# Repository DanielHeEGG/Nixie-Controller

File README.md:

# Nixie-Controller
Yet another nixie clock controller.

See [Hackaday Page](https://hackaday.io/project/180811-open-nixie-controller) for more details.

This project is archived, development is continuing in [v2](https://github.com/DanielHeEGG/Nixie-Controller-v2).

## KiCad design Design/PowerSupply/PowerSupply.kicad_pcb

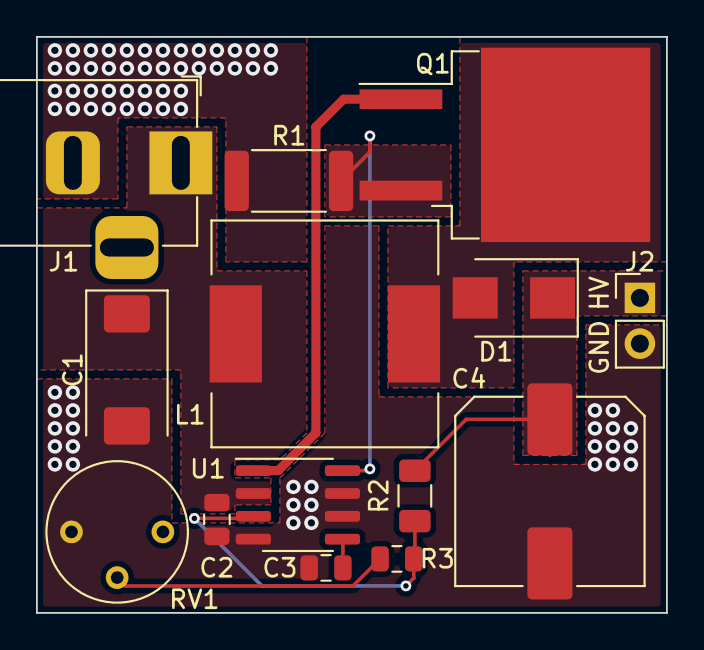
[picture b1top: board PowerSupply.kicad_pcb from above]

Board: 2 copper layers, 35.0 x 32.0 mm, 15 parts (1 on the bottom side), 9 nets.

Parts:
C1: 100uF,Low ESR; CP_EIA-7343-31_Kemet-D
C2, C3: 100nF; C_0805_2012Metric
C4: 10uF,250V; CP_Elec_10x10
CAUTION: Symbol_HighVoltage_Type2_CopperTop_VerySmall
D1: 300V, 2A, Fast Trr; D_SMB
J1: Barrel_Jack; BarrelJack_Horizontal
J2: Conn_01x02_Male; PinHeader_1x02_P2.54mm_Vertical
L1: 100uH,2A; L_12x12mm_H4.5mm
Q1: IRF644; TO-263-2
R1: 0.05,1W; R_2512_6332Metric
R2: 1M2,250V; R_1206_3216Metric
R3: 10K; R_0805_2012Metric
RV1: 10K; Potentiometer_Bourns_3339P_Vertical
U1: MAX1771; SOIC-8_3.9x4.9mm_P1.27mm

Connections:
+12V: C1.1, C2.1, J1.1, L1.1, U1.2
+180V: C4.1, D1.1, J2.1, R2.1
GND: C1.2, C2.2, C3.2, C4.2, J1.2, J2.2, R1.2, RV1.3, U1.4, U1.6, U1.7
unnamed: C3.1, U1.5
unnamed: D1.2, L1.2, Q1.2
unnamed: Q1.1, U1.1
unnamed: Q1.3, R1.1, U1.8
unnamed: R2.2, R3.1, U1.3
unnamed: R3.2, RV1.2

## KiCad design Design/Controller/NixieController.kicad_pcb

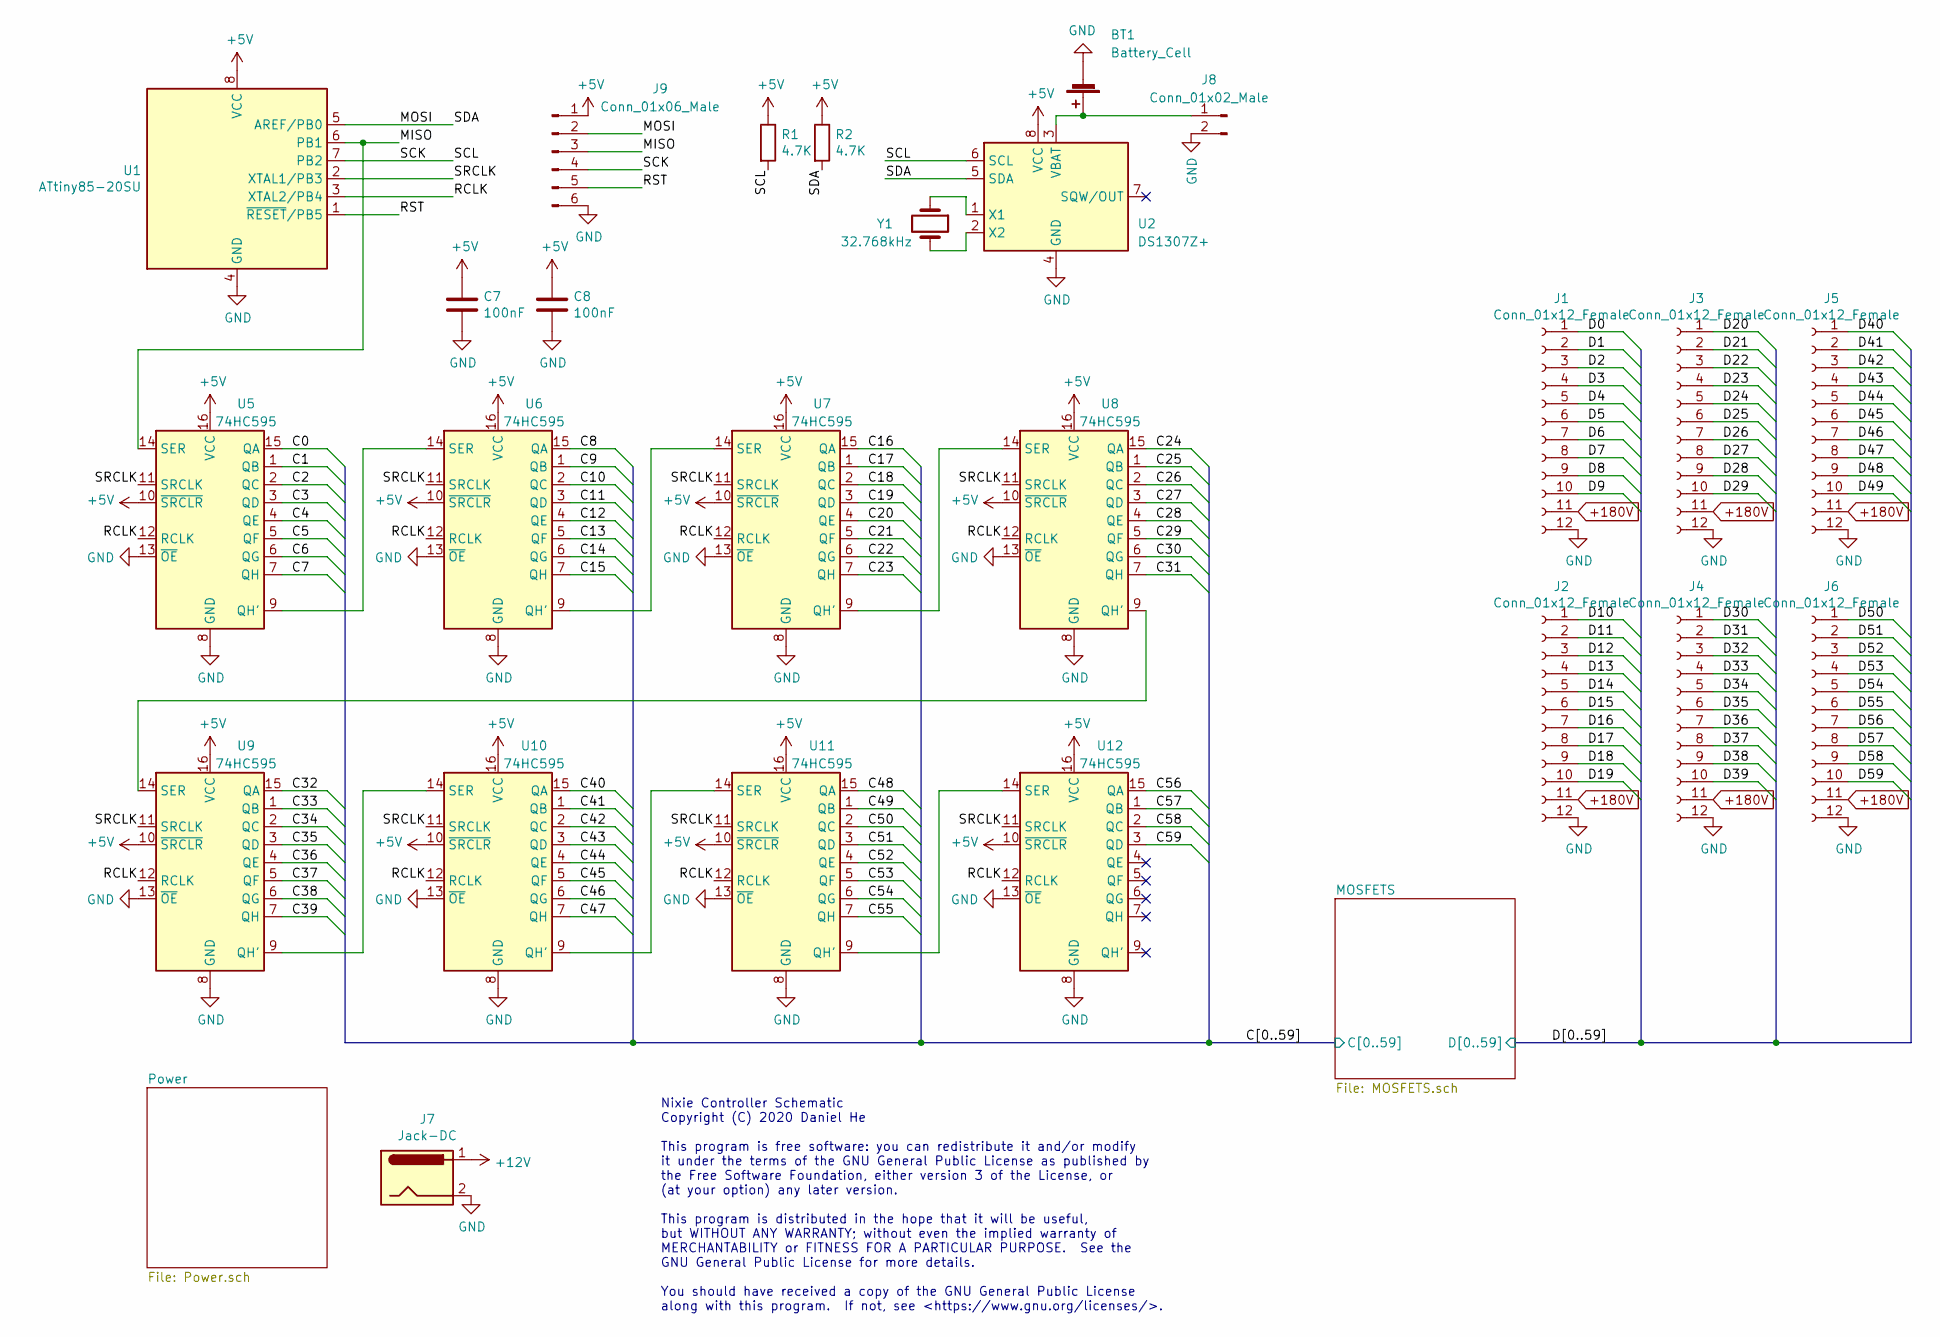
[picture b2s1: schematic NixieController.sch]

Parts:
BT1: Battery_Cell; Keystone_1056
C7, C8: 100nF; C_0805_2012Metric; Digikey # 1276-1007-6-ND
J1, J2, J3, J4, J5, J6: Conn_01x12_Female; PinSocket_1x12_P2.54mm_Vertical
J7: Jack-DC; BarrelJack_Horizontal; Digikey # 2092-KLDX-0202-A-ND
J8: Conn_01x02_Male; PinHeader_1x02_P2.54mm_Vertical
J9: Conn_01x06_Male; PinHeader_1x06_P2.54mm_Vertical
R1, R2: 4.7K; R_0805_2012Metric; Digikey # 311-4.7KARDKR-ND
U1: ATtiny85-20SU; SOIC-8_5.275x5.275mm_P1.27mm; Digikey # ATTINY85-20SURDKR-ND
U2: DS1307Z+; SOIC-8_3.9x4.9mm_P1.27mm; Digikey # DS1307Z+T&RDKR-ND
U5, U6, U7, U8, U9, U10, U11, U12: 74HC595; SOIC-16_3.9x9.9mm_P1.27mm; Digikey # 1727-2821-6-ND
Y1: 32.768kHz; Crystal_SMD_3215-2Pin_3.2x1.5mm; Digikey # SER4103DKR-ND

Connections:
+5V: C7.1, C8.1, J9.1, R1.1, R2.1, U1.8 (VCC), U2.8 (VCC), U5.10 (~SRCLR), U5.16 (VCC), U6.10 (~SRCLR), U6.16 (VCC), U7.10 (~SRCLR), U7.16 (VCC), U8.10 (~SRCLR), U8.16 (VCC), U9.10 (~SRCLR), U9.16 (VCC), U10.10 (~SRCLR), U10.16 (VCC), U11.10 (~SRCLR), U11.16 (VCC), U12.10 (~SRCLR), U12.16 (VCC); also elsewhere on the board
+12V: J7.1; also elsewhere on the board
+180V: J1.11, J2.11, J3.11, J4.11, J5.11, J6.11; also elsewhere on the board
/C0: U5.15 (QA); also elsewhere on the board
/C1: U5.1 (QB); also elsewhere on the board
/C2: U5.2 (QC); also elsewhere on the board
/C3: U5.3 (QD); also elsewhere on the board
/C4: U5.4 (QE); also elsewhere on the board
/C5: U5.5 (QF); also elsewhere on the board
/C6: U5.6 (QG); also elsewhere on the board
/C7: U5.7 (QH); also elsewhere on the board
/C8: U6.15 (QA); also elsewhere on the board
/C9: U6.1 (QB); also elsewhere on the board
/C10: U6.2 (QC); also elsewhere on the board
/C11: U6.3 (QD); also elsewhere on the board
/C12: U6.4 (QE); also elsewhere on the board
/C13: U6.5 (QF); also elsewhere on the board
/C14: U6.6 (QG); also elsewhere on the board
/C15: U6.7 (QH); also elsewhere on the board
/C16: U7.15 (QA); also elsewhere on the board
/C17: U7.1 (QB); also elsewhere on the board
/C18: U7.2 (QC); also elsewhere on the board
/C19: U7.3 (QD); also elsewhere on the board
/C20: U7.4 (QE); also elsewhere on the board
/C21: U7.5 (QF); also elsewhere on the board
/C22: U7.6 (QG); also elsewhere on the board
/C23: U7.7 (QH); also elsewhere on the board
/C24: U8.15 (QA); also elsewhere on the board
/C25: U8.1 (QB); also elsewhere on the board
/C26: U8.2 (QC); also elsewhere on the board
/C27: U8.3 (QD); also elsewhere on the board
/C28: U8.4 (QE); also elsewhere on the board
/C29: U8.5 (QF); also elsewhere on the board
/C30: U8.6 (QG); also elsewhere on the board
/C31: U8.7 (QH); also elsewhere on the board
/C32: U9.15 (QA); also elsewhere on the board
/C33: U9.1 (QB); also elsewhere on the board
/C34: U9.2 (QC); also elsewhere on the board
/C35: U9.3 (QD); also elsewhere on the board
/C36: U9.4 (QE); also elsewhere on the board
/C37: U9.5 (QF); also elsewhere on the board
/C38: U9.6 (QG); also elsewhere on the board
/C39: U9.7 (QH); also elsewhere on the board
/C40: U10.15 (QA); also elsewhere on the board
/C41: U10.1 (QB); also elsewhere on the board
/C42: U10.2 (QC); also elsewhere on the board
/C43: U10.3 (QD); also elsewhere on the board
/C44: U10.4 (QE); also elsewhere on the board
/C45: U10.5 (QF); also elsewhere on the board
/C46: U10.6 (QG); also elsewhere on the board
/C47: U10.7 (QH); also elsewhere on the board
/C48: U11.15 (QA); also elsewhere on the board
/C49: U11.1 (QB); also elsewhere on the board
/C50: U11.2 (QC); also elsewhere on the board
/C51: U11.3 (QD); also elsewhere on the board
/C52: U11.4 (QE); also elsewhere on the board
/C53: U11.5 (QF); also elsewhere on the board
/C54: U11.6 (QG); also elsewhere on the board
/C55: U11.7 (QH); also elsewhere on the board
/C56: U12.15 (QA); also elsewhere on the board
/C57: U12.1 (QB); also elsewhere on the board
/C58: U12.2 (QC); also elsewhere on the board
/C59: U12.3 (QD); also elsewhere on the board
/D0: J1.1; also elsewhere on the board
/D1: J1.2; also elsewhere on the board
/D2: J1.3; also elsewhere on the board
/D3: J1.4; also elsewhere on the board
/D4: J1.5; also elsewhere on the board
/D5: J1.6; also elsewhere on the board
/D6: J1.7; also elsewhere on the board
/D7: J1.8; also elsewhere on the board
/D8: J1.9; also elsewhere on the board
/D9: J1.10; also elsewhere on the board
/D10: J2.1; also elsewhere on the board
/D11: J2.2; also elsewhere on the board
/D12: J2.3; also elsewhere on the board
/D13: J2.4; also elsewhere on the board
/D14: J2.5; also elsewhere on the board
/D15: J2.6; also elsewhere on the board
/D16: J2.7; also elsewhere on the board
/D17: J2.8; also elsewhere on the board
/D18: J2.9; also elsewhere on the board
/D19: J2.10; also elsewhere on the board
/D20: J3.1; also elsewhere on the board
/D21: J3.2; also elsewhere on the board
/D22: J3.3; also elsewhere on the board
/D23: J3.4; also elsewhere on the board
/D24: J3.5; also elsewhere on the board
/D25: J3.6; also elsewhere on the board
/D26: J3.7; also elsewhere on the board
/D27: J3.8; also elsewhere on the board
/D28: J3.9; also elsewhere on the board
/D29: J3.10; also elsewhere on the board
/D30: J4.1; also elsewhere on the board
/D31: J4.2; also elsewhere on the board
/D32: J4.3; also elsewhere on the board
/D33: J4.4; also elsewhere on the board
/D34: J4.5; also elsewhere on the board
/D35: J4.6; also elsewhere on the board
/D36: J4.7; also elsewhere on the board
/D37: J4.8; also elsewhere on the board
/D38: J4.9; also elsewhere on the board
/D39: J4.10; also elsewhere on the board
/D40: J5.1; also elsewhere on the board
/D41: J5.2; also elsewhere on the board
/D42: J5.3; also elsewhere on the board
/D43: J5.4; also elsewhere on the board
/D44: J5.5; also elsewhere on the board
/D45: J5.6; also elsewhere on the board
/D46: J5.7; also elsewhere on the board
/D47: J5.8; also elsewhere on the board
/D48: J5.9; also elsewhere on the board
/D49: J5.10; also elsewhere on the board
/D50: J6.1; also elsewhere on the board
/D51: J6.2; also elsewhere on the board
/D52: J6.3; also elsewhere on the board
/D53: J6.4; also elsewhere on the board
/D54: J6.5; also elsewhere on the board
/D55: J6.6; also elsewhere on the board
/D56: J6.7; also elsewhere on the board
/D57: J6.8; also elsewhere on the board
/D58: J6.9; also elsewhere on the board
/D59: J6.10; also elsewhere on the board
/MISO: J9.3, U1.6 (PB1), U5.14 (SER)
/MOSI: J9.2, R2.2, U1.5 (AREF/PB0), U2.5 (SDA)
/RCLK: U1.3 (XTAL2/PB4), U5.12 (RCLK), U6.12 (RCLK), U7.12 (RCLK), U8.12 (RCLK), U9.12 (RCLK), U10.12 (RCLK), U11.12 (RCLK), U12.12 (RCLK)
/RST: J9.5, U1.1 (~RESET~/PB5)
/SCK: J9.4, R1.2, U1.7 (PB2), U2.6 (SCL)
/SRCLK: U1.2 (XTAL1/PB3), U5.11 (SRCLK), U6.11 (SRCLK), U7.11 (SRCLK), U8.11 (SRCLK), U9.11 (SRCLK), U10.11 (SRCLK), U11.11 (SRCLK), U12.11 (SRCLK)
GND: BT1.2 (-), C7.2, C8.2, J1.12, J2.12, J3.12, J4.12, J5.12, J6.12, J7.2, J8.2, J9.6, U1.4 (GND), U2.4 (GND), U5.8 (GND), U5.13 (~OE), U6.8 (GND), U6.13 (~OE), U7.8 (GND), U7.13 (~OE), U8.8 (GND), U8.13 (~OE), U9.8 (GND), U9.13 (~OE), U10.8 (GND), U10.13 (~OE), U11.8 (GND), U11.13 (~OE), U12.8 (GND), U12.13 (~OE); also elsewhere on the board
unnamed: BT1.1 (+), J8.1, U2.3 (VBAT)
unnamed: U2.1 (X1), Y1.1
unnamed: U2.2 (X2), Y1.2
unnamed: U5.9 (QH'), U6.14 (SER)
unnamed: U6.9 (QH'), U7.14 (SER)
unnamed: U7.9 (QH'), U8.14 (SER)
unnamed: U8.9 (QH'), U9.14 (SER)
unnamed: U10.9 (QH'), U11.14 (SER)
unnamed: U9.9 (QH'), U10.14 (SER)
unnamed: U11.9 (QH'), U12.14 (SER)

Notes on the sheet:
Nixie Controller Schematic Copyright (C) 2020 Daniel He This program is free software: you can redistribute it and/or modify it under the terms of the GNU General Public License as published by the Free Software Foundation, either version 3 of the License, or (at your option) any later version. Thi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

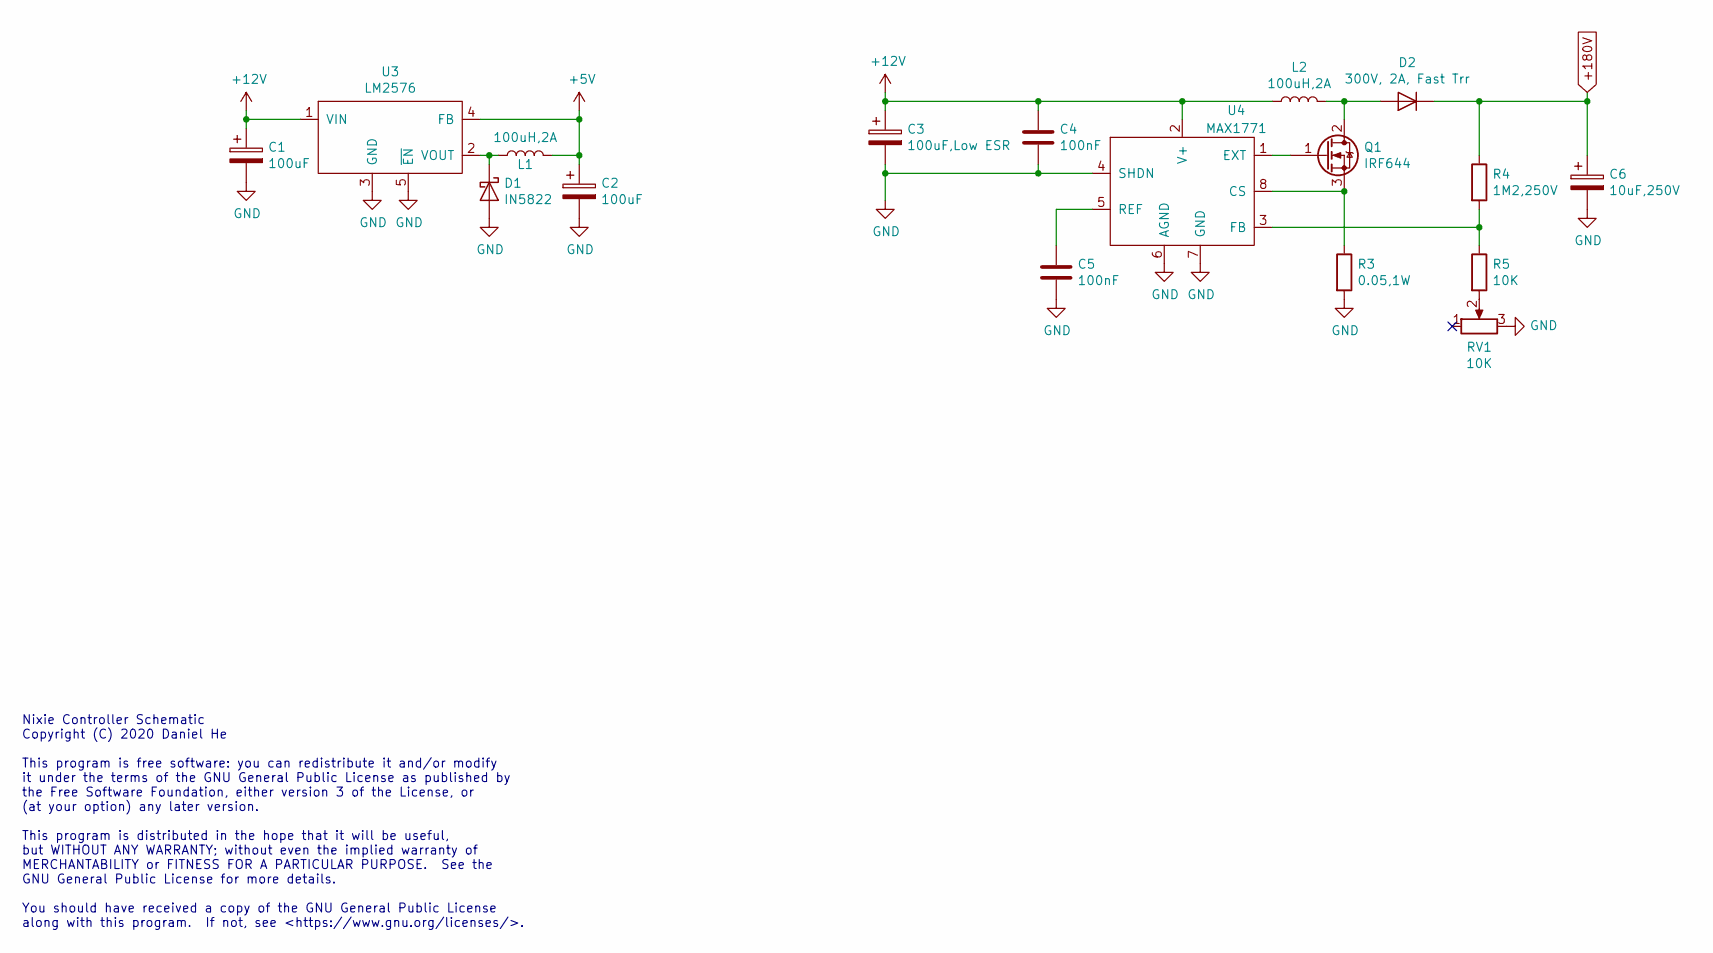
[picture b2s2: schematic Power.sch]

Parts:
C1, C2: 100uF; CP_Elec_6.3x7.7; Digikey # PCE3898DKR-ND
C3: 100uF,Low ESR; CP_EIA-7343-31_Kemet-D; Digikey # 478-TPSD107M020R0150DKR-ND
C4, C5: 100nF; C_0805_2012Metric; Digikey # 1276-1007-6-ND
C6: 10uF,250V; CP_Elec_10x10; Digikey # PCE3432DKR-ND
D1: IN5822; D_DO-201AD_P12.70mm_Horizontal; Digikey # 1N5822-E3/54GITR-ND
D2: 300V, 2A, Fast Trr; D_SMB; Digikey # ES2F-E3/52TGIDKR-ND
L1, L2: 100uH,2A; L_12x12mm_H4.5mm; Digikey # 513-1526-6-ND
Q1: IRF644; TO-263-2; Digikey # IRF644STRLPBFDKR-ND
R3: 0.05,1W; R_2512_6332Metric; Digikey # YAG2156DKR-ND
R4: 1M2,250V; R_1206_3216Metric; Digikey # 311-1.2MERDKR-ND
R5: 10K; R_0805_2012Metric; Digikey # 311-10KARDKR-ND
RV1: 10K; Potentiometer_Bourns_3339P_Vertical; Digikey # 3362P-502LF-ND
U3: LM2576; TO-263-5_TabPin3; Digikey # LM2576SX-5.0/NOPBDKR-ND
U4: MAX1771; SOIC-8_3.9x4.9mm_P1.27mm; Digikey # MAX1771CSA+DKR-ND

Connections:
+5V: C2.1, L1.2, U3.4 (FB); also elsewhere on the board
+12V: C1.1, C3.1, C4.1, L2.1, U3.1 (VIN), U4.2 (V+); also elsewhere on the board
+180V: C6.1, D2.1 (K), R4.1; also elsewhere on the board
GND: C1.2, C2.2, C3.2, C4.2, C5.2, C6.2, D1.2 (A), R3.2, RV1.3, U3.3 (GND), U3.5 (~EN), U4.4 (SHDN), U4.6 (AGND), U4.7 (GND); also elsewhere on the board
unnamed: C5.1, U4.5 (REF)
unnamed: D1.1 (K), L1.1, U3.2 (VOUT)
unnamed: D2.2 (A), L2.2, Q1.2 (D)
unnamed: Q1.1 (G), U4.1 (EXT)
unnamed: Q1.3 (S), R3.1, U4.8 (CS)
unnamed: R4.2, R5.1, U4.3 (FB)
unnamed: R5.2, RV1.2

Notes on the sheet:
Nixie Controller Schematic Copyright (C) 2020 Daniel He This program is free software: you can redistribute it and/or modify it under the terms of the GNU General Public License as published by the Free Software Foundation, either version 3 of the License, or (at your option) any later version. Thi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

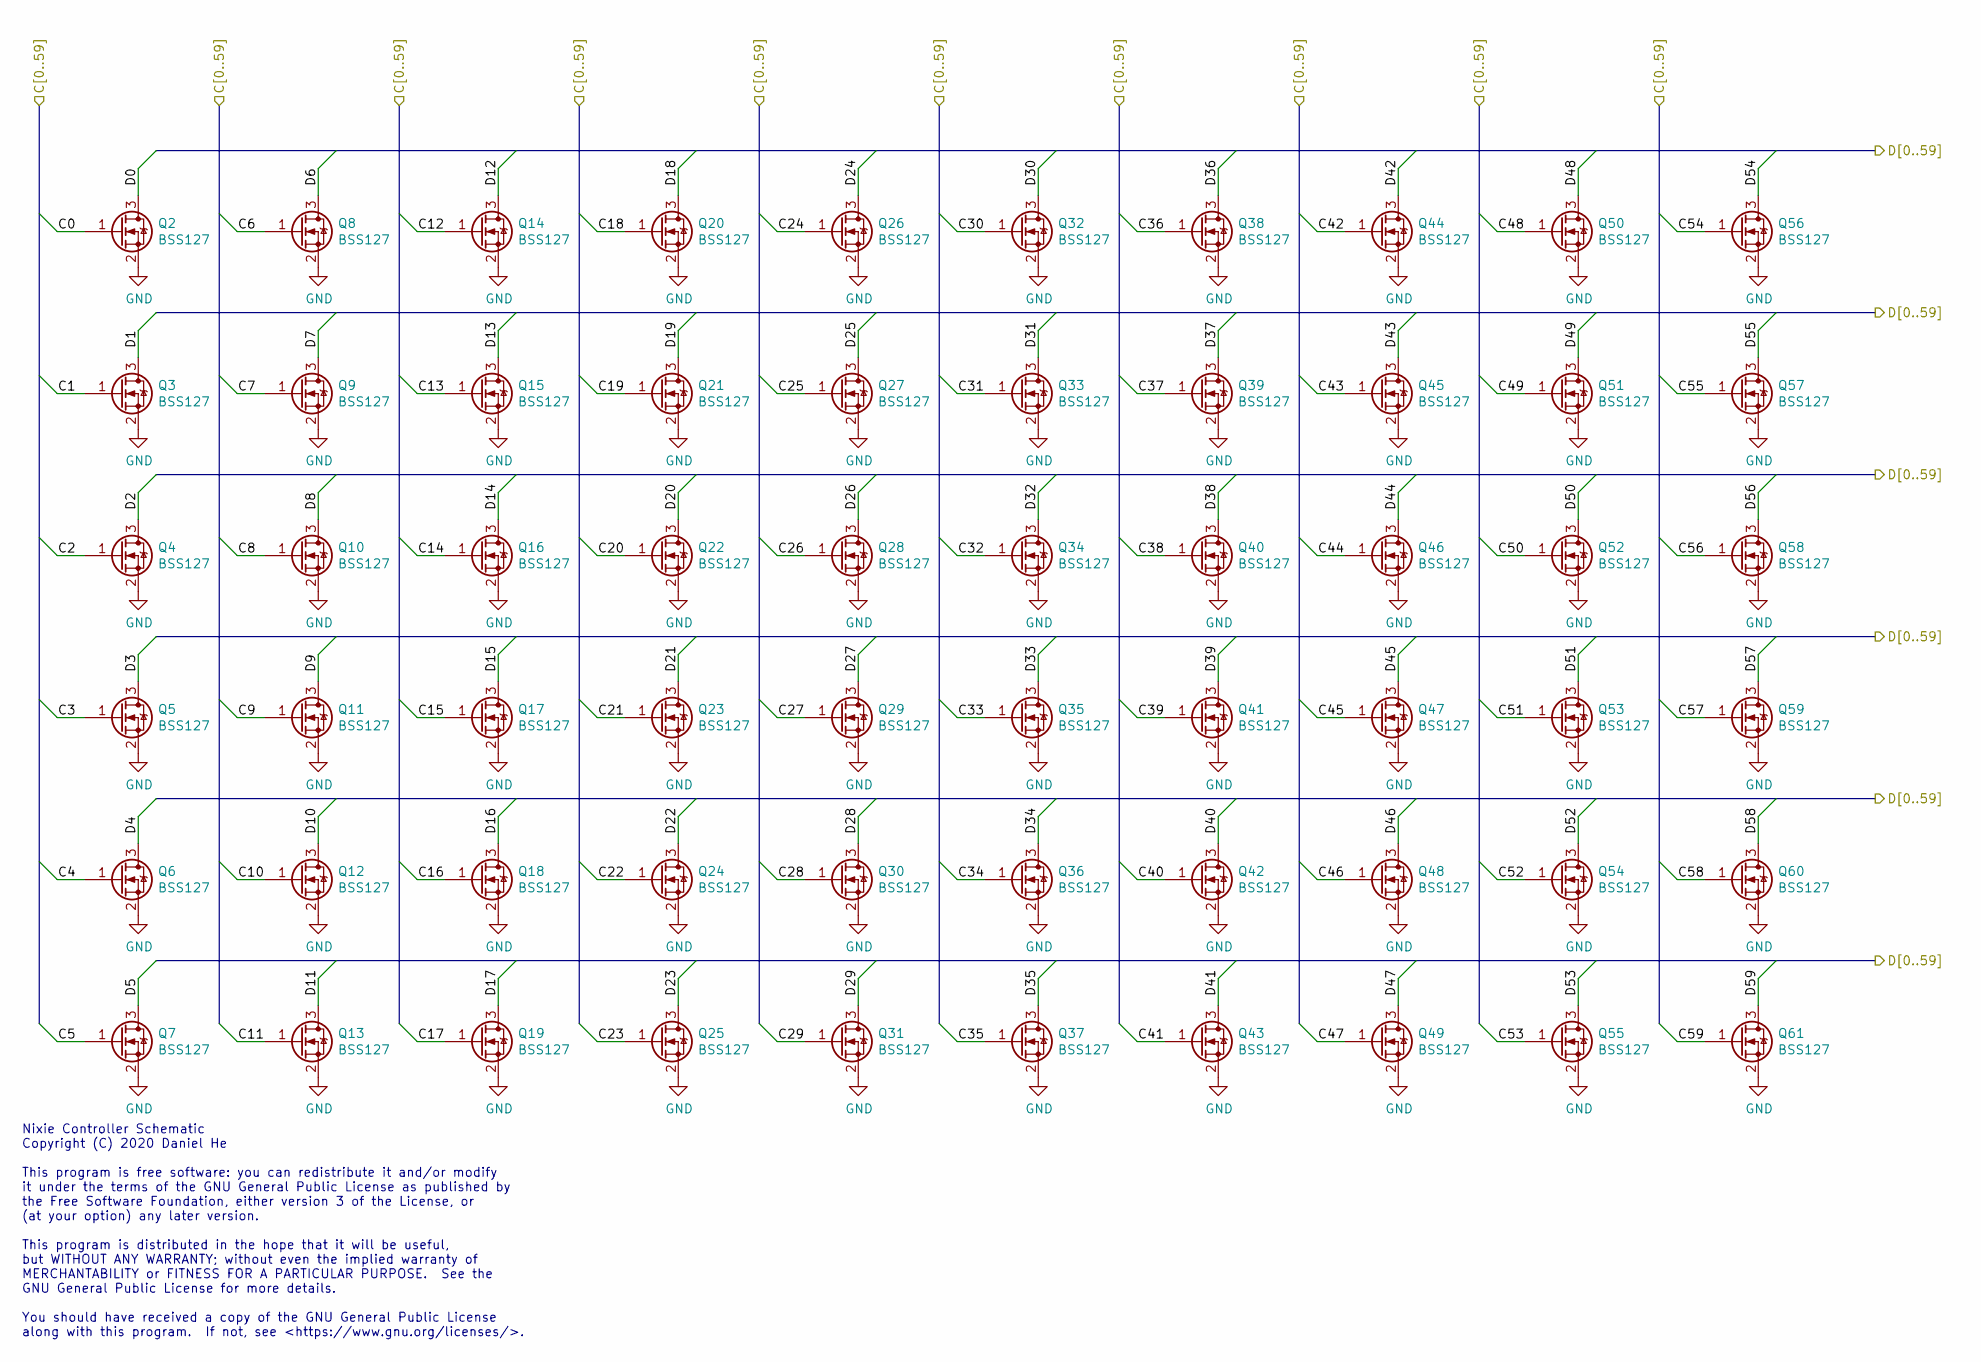
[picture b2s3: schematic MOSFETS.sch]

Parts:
Q2, Q3, Q4, Q5, Q6, Q7, Q8, Q9, Q10, Q11, Q12, Q13, Q14, Q15, Q16, Q17, Q18, Q19, Q20, Q21, Q22, Q23, Q24, Q25, Q26, Q27, Q28, Q29, Q30, Q31, Q32, Q33, Q34, Q35, Q36, Q37, Q38, Q39, Q40, Q41, Q42, Q43, Q44, Q45, Q46, Q47, Q48, Q49, Q50, Q51, Q52, Q53, Q54, Q55, Q56, Q57, Q58, Q59, Q60, Q61: BSS127; SOT-23; Digikey # BSS127S-7DIDKR-ND

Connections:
/C0: Q2.1 (G); also elsewhere on the board
/C1: Q3.1 (G); also elsewhere on the board
/C2: Q4.1 (G); also elsewhere on the board
/C3: Q5.1 (G); also elsewhere on the board
/C4: Q6.1 (G); also elsewhere on the board
/C5: Q7.1 (G); also elsewhere on the board
/C6: Q8.1 (G); also elsewhere on the board
/C7: Q9.1 (G); also elsewhere on the board
/C8: Q10.1 (G); also elsewhere on the board
/C9: Q11.1 (G); also elsewhere on the board
/C10: Q12.1 (G); also elsewhere on the board
/C11: Q13.1 (G); also elsewhere on the board
/C12: Q14.1 (G); also elsewhere on the board
/C13: Q15.1 (G); also elsewhere on the board
/C14: Q16.1 (G); also elsewhere on the board
/C15: Q17.1 (G); also elsewhere on the board
/C16: Q18.1 (G); also elsewhere on the board
/C17: Q19.1 (G); also elsewhere on the board
/C18: Q20.1 (G); also elsewhere on the board
/C19: Q21.1 (G); also elsewhere on the board
/C20: Q22.1 (G); also elsewhere on the board
/C21: Q23.1 (G); also elsewhere on the board
/C22: Q24.1 (G); also elsewhere on the board
/C23: Q25.1 (G); also elsewhere on the board
/C24: Q26.1 (G); also elsewhere on the board
/C25: Q27.1 (G); also elsewhere on the board
/C26: Q28.1 (G); also elsewhere on the board
/C27: Q29.1 (G); also elsewhere on the board
/C28: Q30.1 (G); also elsewhere on the board
/C29: Q31.1 (G); also elsewhere on the board
/C30: Q32.1 (G); also elsewhere on the board
/C31: Q33.1 (G); also elsewhere on the board
/C32: Q34.1 (G); also elsewhere on the board
/C33: Q35.1 (G); also elsewhere on the board
/C34: Q36.1 (G); also elsewhere on the board
/C35: Q37.1 (G); also elsewhere on the board
/C36: Q38.1 (G); also elsewhere on the board
/C37: Q39.1 (G); also elsewhere on the board
/C38: Q40.1 (G); also elsewhere on the board
/C39: Q41.1 (G); also elsewhere on the board
/C40: Q42.1 (G); also elsewhere on the board
/C41: Q43.1 (G); also elsewhere on the board
/C42: Q44.1 (G); also elsewhere on the board
/C43: Q45.1 (G); also elsewhere on the board
/C44: Q46.1 (G); also elsewhere on the board
/C45: Q47.1 (G); also elsewhere on the board
/C46: Q48.1 (G); also elsewhere on the board
/C47: Q49.1 (G); also elsewhere on the board
/C48: Q50.1 (G); also elsewhere on the board
/C49: Q51.1 (G); also elsewhere on the board
/C50: Q52.1 (G); also elsewhere on the board
/C51: Q53.1 (G); also elsewhere on the board
/C52: Q54.1 (G); also elsewhere on the board
/C53: Q55.1 (G); also elsewhere on the board
/C54: Q56.1 (G); also elsewhere on the board
/C55: Q57.1 (G); also elsewhere on the board
/C56: Q58.1 (G); also elsewhere on the board
/C57: Q59.1 (G); also elsewhere on the board
/C58: Q60.1 (G); also elsewhere on the board
/C59: Q61.1 (G); also elsewhere on the board
/D0: Q2.3 (D); also elsewhere on the board
/D1: Q3.3 (D); also elsewhere on the board
/D2: Q4.3 (D); also elsewhere on the board
/D3: Q5.3 (D); also elsewhere on the board
/D4: Q6.3 (D); also elsewhere on the board
/D5: Q7.3 (D); also elsewhere on the board
/D6: Q8.3 (D); also elsewhere on the board
/D7: Q9.3 (D); also elsewhere on the board
/D8: Q10.3 (D); also elsewhere on the board
/D9: Q11.3 (D); also elsewhere on the board
/D10: Q12.3 (D); also elsewhere on the board
/D11: Q13.3 (D); also elsewhere on the board
/D12: Q14.3 (D); also elsewhere on the board
/D13: Q15.3 (D); also elsewhere on the board
/D14: Q16.3 (D); also elsewhere on the board
/D15: Q17.3 (D); also elsewhere on the board
/D16: Q18.3 (D); also elsewhere on the board
/D17: Q19.3 (D); also elsewhere on the board
/D18: Q20.3 (D); also elsewhere on the board
/D19: Q21.3 (D); also elsewhere on the board
/D20: Q22.3 (D); also elsewhere on the board
/D21: Q23.3 (D); also elsewhere on the board
/D22: Q24.3 (D); also elsewhere on the board
/D23: Q25.3 (D); also elsewhere on the board
/D24: Q26.3 (D); also elsewhere on the board
/D25: Q27.3 (D); also elsewhere on the board
/D26: Q28.3 (D); also elsewhere on the board
/D27: Q29.3 (D); also elsewhere on the board
/D28: Q30.3 (D); also elsewhere on the board
/D29: Q31.3 (D); also elsewhere on the board
/D30: Q32.3 (D); also elsewhere on the board
/D31: Q33.3 (D); also elsewhere on the board
/D32: Q34.3 (D); also elsewhere on the board
/D33: Q35.3 (D); also elsewhere on the board
/D34: Q36.3 (D); also elsewhere on the board
/D35: Q37.3 (D); also elsewhere on the board
/D36: Q38.3 (D); also elsewhere on the board
/D37: Q39.3 (D); also elsewhere on the board
/D38: Q40.3 (D); also elsewhere on the board
/D39: Q41.3 (D); also elsewhere on the board
/D40: Q42.3 (D); also elsewhere on the board
/D41: Q43.3 (D); also elsewhere on the board
/D42: Q44.3 (D); also elsewhere on the board
/D43: Q45.3 (D); also elsewhere on the board
/D44: Q46.3 (D); also elsewhere on the board
/D45: Q47.3 (D); also elsewhere on the board
/D46: Q48.3 (D); also elsewhere on the board
/D47: Q49.3 (D); also elsewhere on the board
/D48: Q50.3 (D); also elsewhere on the board
/D49: Q51.3 (D); also elsewhere on the board
/D50: Q52.3 (D); also elsewhere on the board
/D51: Q53.3 (D); also elsewhere on the board
/D52: Q54.3 (D); also elsewhere on the board
/D53: Q55.3 (D); also elsewhere on the board
/D54: Q56.3 (D); also elsewhere on the board
/D55: Q57.3 (D); also elsewhere on the board
/D56: Q58.3 (D); also elsewhere on the board
/D57: Q59.3 (D); also elsewhere on the board
/D58: Q60.3 (D); also elsewhere on the board
/D59: Q61.3 (D); also elsewhere on the board
GND: Q2.2 (S), Q3.2 (S), Q4.2 (S), Q5.2 (S), Q6.2 (S), Q7.2 (S), Q8.2 (S), Q9.2 (S), Q10.2 (S), Q11.2 (S), Q12.2 (S), Q13.2 (S), Q14.2 (S), Q15.2 (S), Q16.2 (S), Q17.2 (S), Q18.2 (S), Q19.2 (S), Q20.2 (S), Q21.2 (S), Q22.2 (S), Q23.2 (S), Q24.2 (S), Q25.2 (S), Q26.2 (S), Q27.2 (S), Q28.2 (S), Q29.2 (S), Q30.2 (S), Q31.2 (S), Q32.2 (S), Q33.2 (S), Q34.2 (S), Q35.2 (S), Q36.2 (S), Q37.2 (S), Q38.2 (S), Q39.2 (S), Q40.2 (S), Q41.2 (S), Q42.2 (S), Q43.2 (S), Q44.2 (S), Q45.2 (S), Q46.2 (S), Q47.2 (S), Q48.2 (S), Q49.2 (S), Q50.2 (S), Q51.2 (S), Q52.2 (S), Q53.2 (S), Q54.2 (S), Q55.2 (S), Q56.2 (S), Q57.2 (S), Q58.2 (S), Q59.2 (S), Q60.2 (S), Q61.2 (S); also elsewhere on the board

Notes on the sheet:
Nixie Controller Schematic Copyright (C) 2020 Daniel He This program is free software: you can redistribute it and/or modify it under the terms of the GNU General Public License as published by the Free Software Foundation, either version 3 of the License, or (at your option) any later version. Thi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

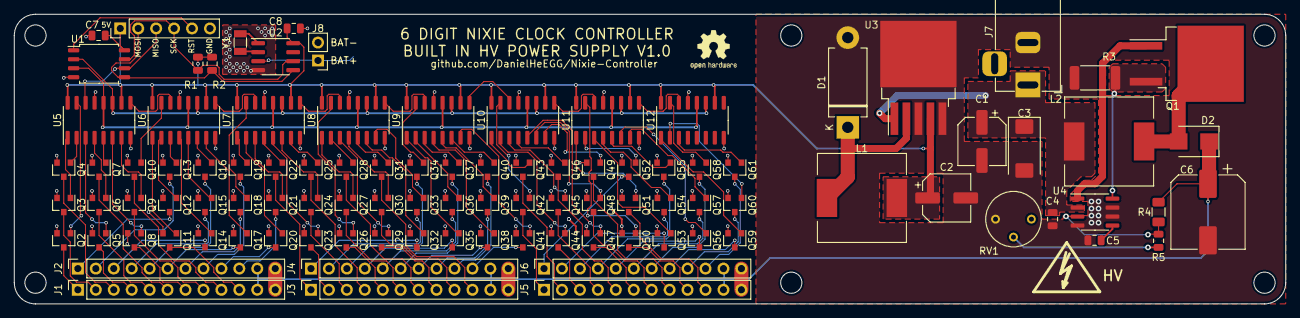
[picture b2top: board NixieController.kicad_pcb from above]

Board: 2 copper layers, 180.0 x 41.0 mm, 102 parts (1 on the bottom side), 147 nets.

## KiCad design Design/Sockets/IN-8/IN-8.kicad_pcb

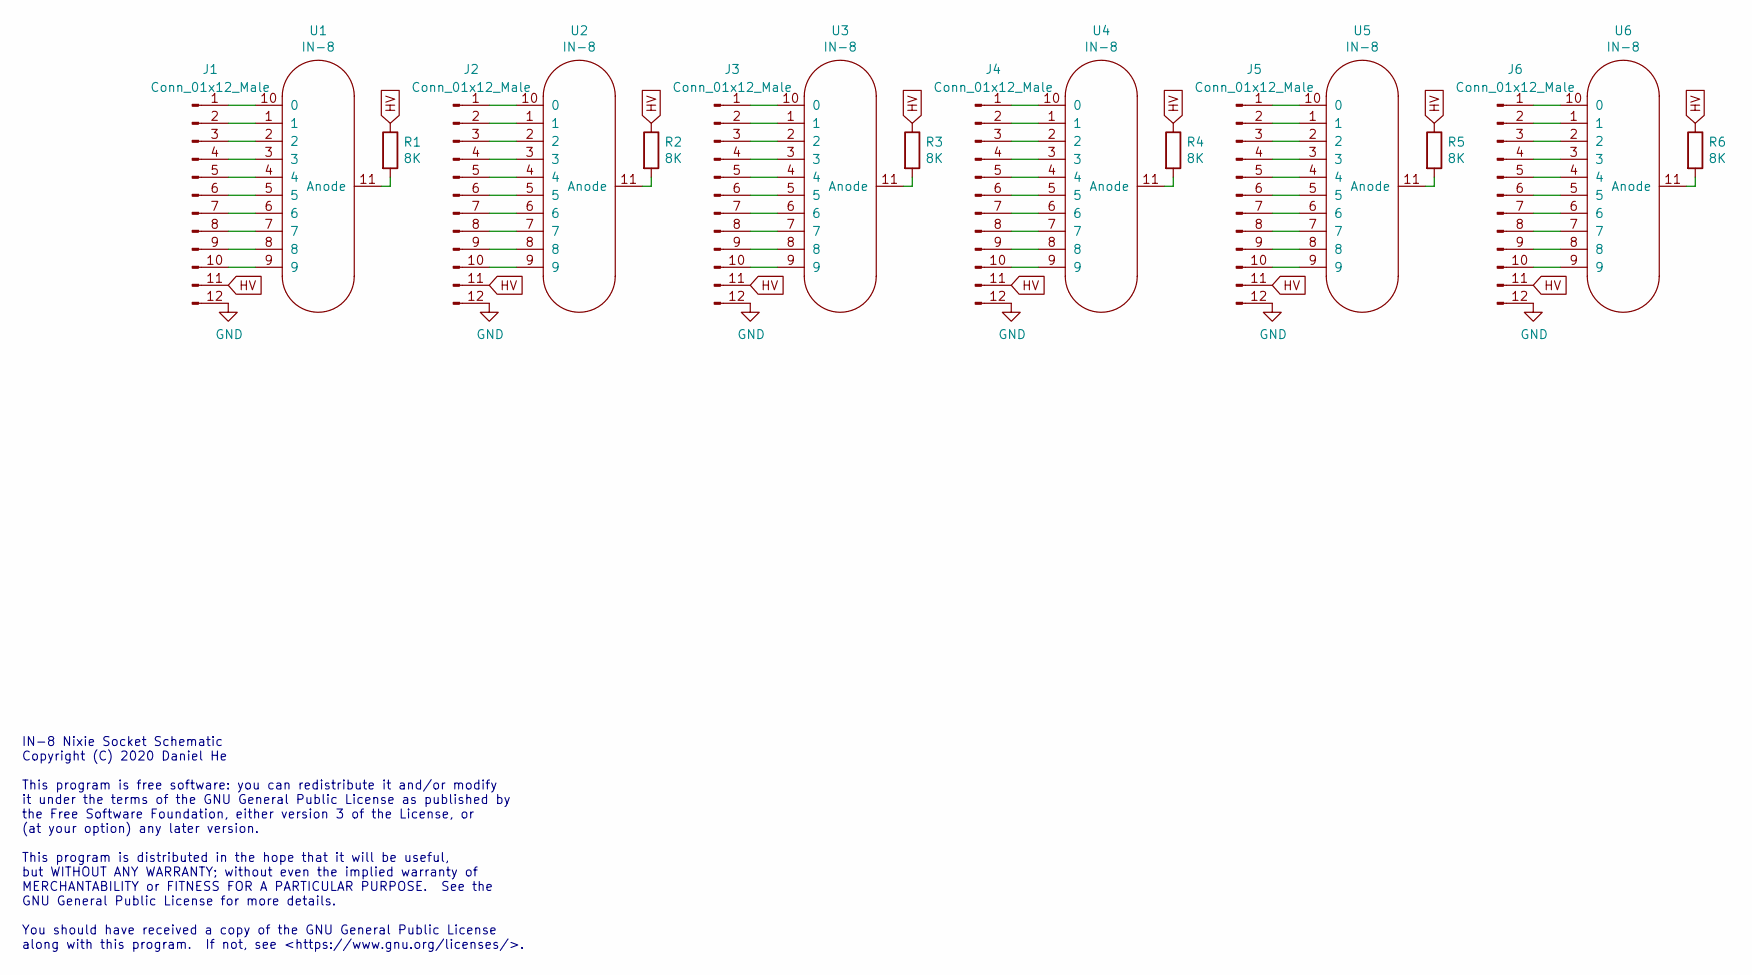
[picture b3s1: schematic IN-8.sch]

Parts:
J1, J2, J3, J4, J5, J6: Conn_01x12_Male; PinHeader_1x12_P2.54mm_Vertical
R1, R2, R3, R4, R5, R6: 8K; R_0805_2012Metric
U1, U2, U3, U4, U5, U6: IN-8

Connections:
GND: J1.12, J2.12, J3.12, J4.12, J5.12, J6.12
HV: J1.11, J2.11, J3.11, J4.11, J5.11, J6.11, R1.1, R2.1, R3.1, R4.1, R5.1, R6.1
unnamed: J1.1, U1.10 (0)
unnamed: J1.2, U1.1
unnamed: J1.3, U1.2
unnamed: J1.4, U1.3
unnamed: J1.5, U1.4
unnamed: J1.6, U1.5
unnamed: J1.7, U1.6
unnamed: J1.8, U1.7
unnamed: J1.9, U1.8
unnamed: J1.10, U1.9
unnamed: J2.1, U2.10 (0)
unnamed: J2.2, U2.1
unnamed: J2.3, U2.2
unnamed: J2.4, U2.3
unnamed: J2.5, U2.4
unnamed: J2.6, U2.5
unnamed: J2.7, U2.6
unnamed: J2.8, U2.7
unnamed: J2.9, U2.8
unnamed: J2.10, U2.9
unnamed: J3.1, U3.10 (0)
unnamed: J3.2, U3.1
unnamed: J3.3, U3.2
unnamed: J3.4, U3.3
unnamed: J3.5, U3.4
unnamed: J3.6, U3.5
unnamed: J3.7, U3.6
unnamed: J3.8, U3.7
unnamed: J3.9, U3.8
unnamed: J3.10, U3.9
unnamed: J4.1, U4.10 (0)
unnamed: J4.2, U4.1
unnamed: J4.3, U4.2
unnamed: J4.4, U4.3
unnamed: J4.5, U4.4
unnamed: J4.6, U4.5
unnamed: J4.7, U4.6
unnamed: J4.8, U4.7
unnamed: J4.9, U4.8
unnamed: J4.10, U4.9
unnamed: J5.1, U5.10 (0)
unnamed: J5.2, U5.1
unnamed: J5.3, U5.2
unnamed: J5.4, U5.3
unnamed: J5.5, U5.4
unnamed: J5.6, U5.5
unnamed: J5.7, U5.6
unnamed: J5.8, U5.7
unnamed: J5.9, U5.8
unnamed: J5.10, U5.9
unnamed: J6.1, U6.10 (0)
unnamed: J6.2, U6.1
unnamed: J6.3, U6.2
unnamed: J6.4, U6.3
unnamed: J6.5, U6.4
unnamed: J6.6, U6.5
unnamed: J6.7, U6.6
unnamed: J6.8, U6.7
unnamed: J6.9, U6.8
unnamed: J6.10, U6.9
unnamed: R1.2, U1.11 (Anode)
unnamed: R2.2, U2.11 (Anode)
unnamed: R3.2, U3.11 (Anode)
unnamed: R4.2, U4.11 (Anode)
unnamed: R5.2, U5.11 (Anode)
unnamed: R6.2, U6.11 (Anode)

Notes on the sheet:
IN-8 Nixie Socket Schematic Copyright (C) 2020 Daniel He This program is free software: you can redistribute it and/or modify it under the terms of the GNU General Public License as published by the Free Software Foundation, either version 3 of the License, or (at your option) any later version. Th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

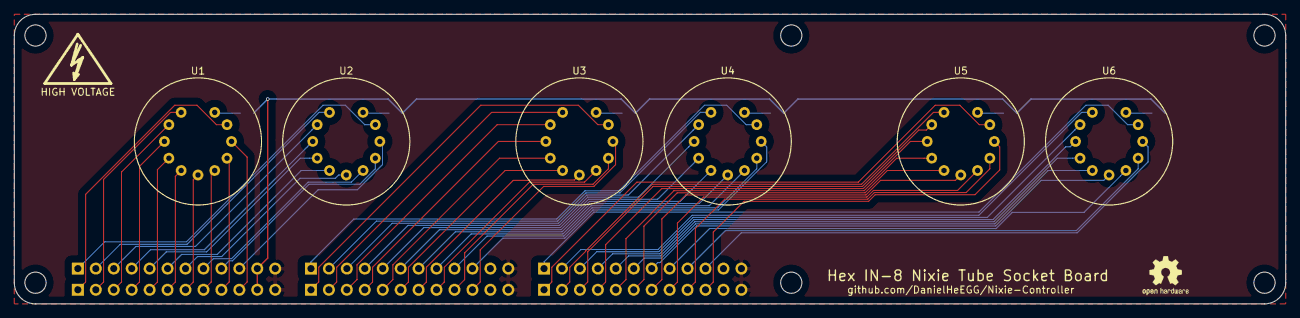
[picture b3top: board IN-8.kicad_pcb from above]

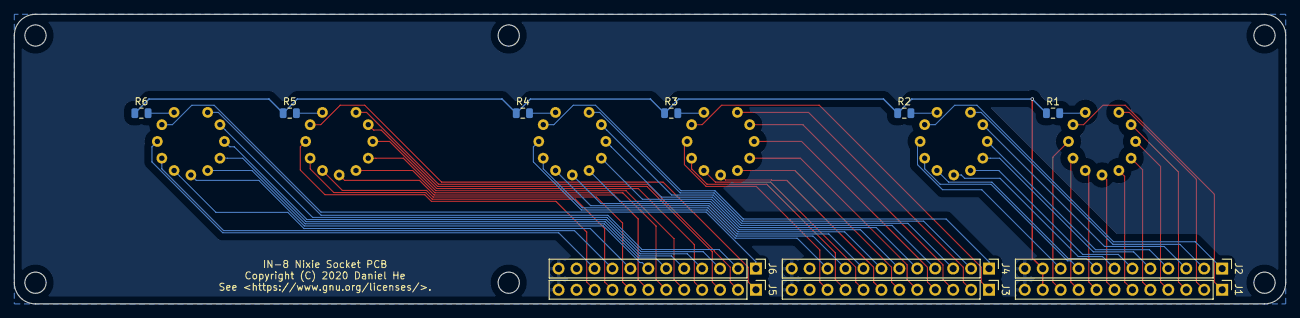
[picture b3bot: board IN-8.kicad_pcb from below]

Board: 2 copper layers, 180.0 x 41.0 mm, 18 parts (12 on the bottom side), 68 nets.
